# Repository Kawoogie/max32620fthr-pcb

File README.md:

# MAX32620FTHR PCB CAD Data

## Files
File Name | Description
--- | ---
max32620fthr.brd  | Cadsoft Eagle Board File (7.5.0)
max32620fthr.sch  | Cadsoft Eagle Schematic File (7.5.0)
output-gerb274x_4layer.cam  | Cadsoft Eagle CAM Job (7.5.0)
output/max32620fthr.gpi  | Photoplotter Info File
output/max32620fthr.GTL  | Top (1) copper
output/max32620fthr.GTS  | Top soldermask
output/max32620fthr.GTO  | Top silk screen
output/max32620fthr.GTP  | Top paste
output/max32620fthr.G2L  | Inner GND (2) copper
output/max32620fthr.G3L  | Inner PWR (15) copper
output/max32620fthr.GBL  | Bottom (16) copper
output/max32620fthr.GBS  | Bottom soldermask
output/max32620fthr.GBO  | Bottom silk screen
output/max32620fthr.GFD  | Fab drawing
output/max32620fthr.GML  | Mill Layer
output/max32620fthr.dri  | Drill Station Info File
output/max32620fthr.TXT  | Excellon Drill File
output/max32620fthr.mnt  | Component XY Data File
output/max32620fthr_sch.pdf  | PDF Schematic
output/max32620fthr_fab.PDF  | PDF Fab Drawing

## Bill Of Materials
[Octopart MAX32620FTHR BOM](https://octopart.com/bom-tool/neiQ2i4s)

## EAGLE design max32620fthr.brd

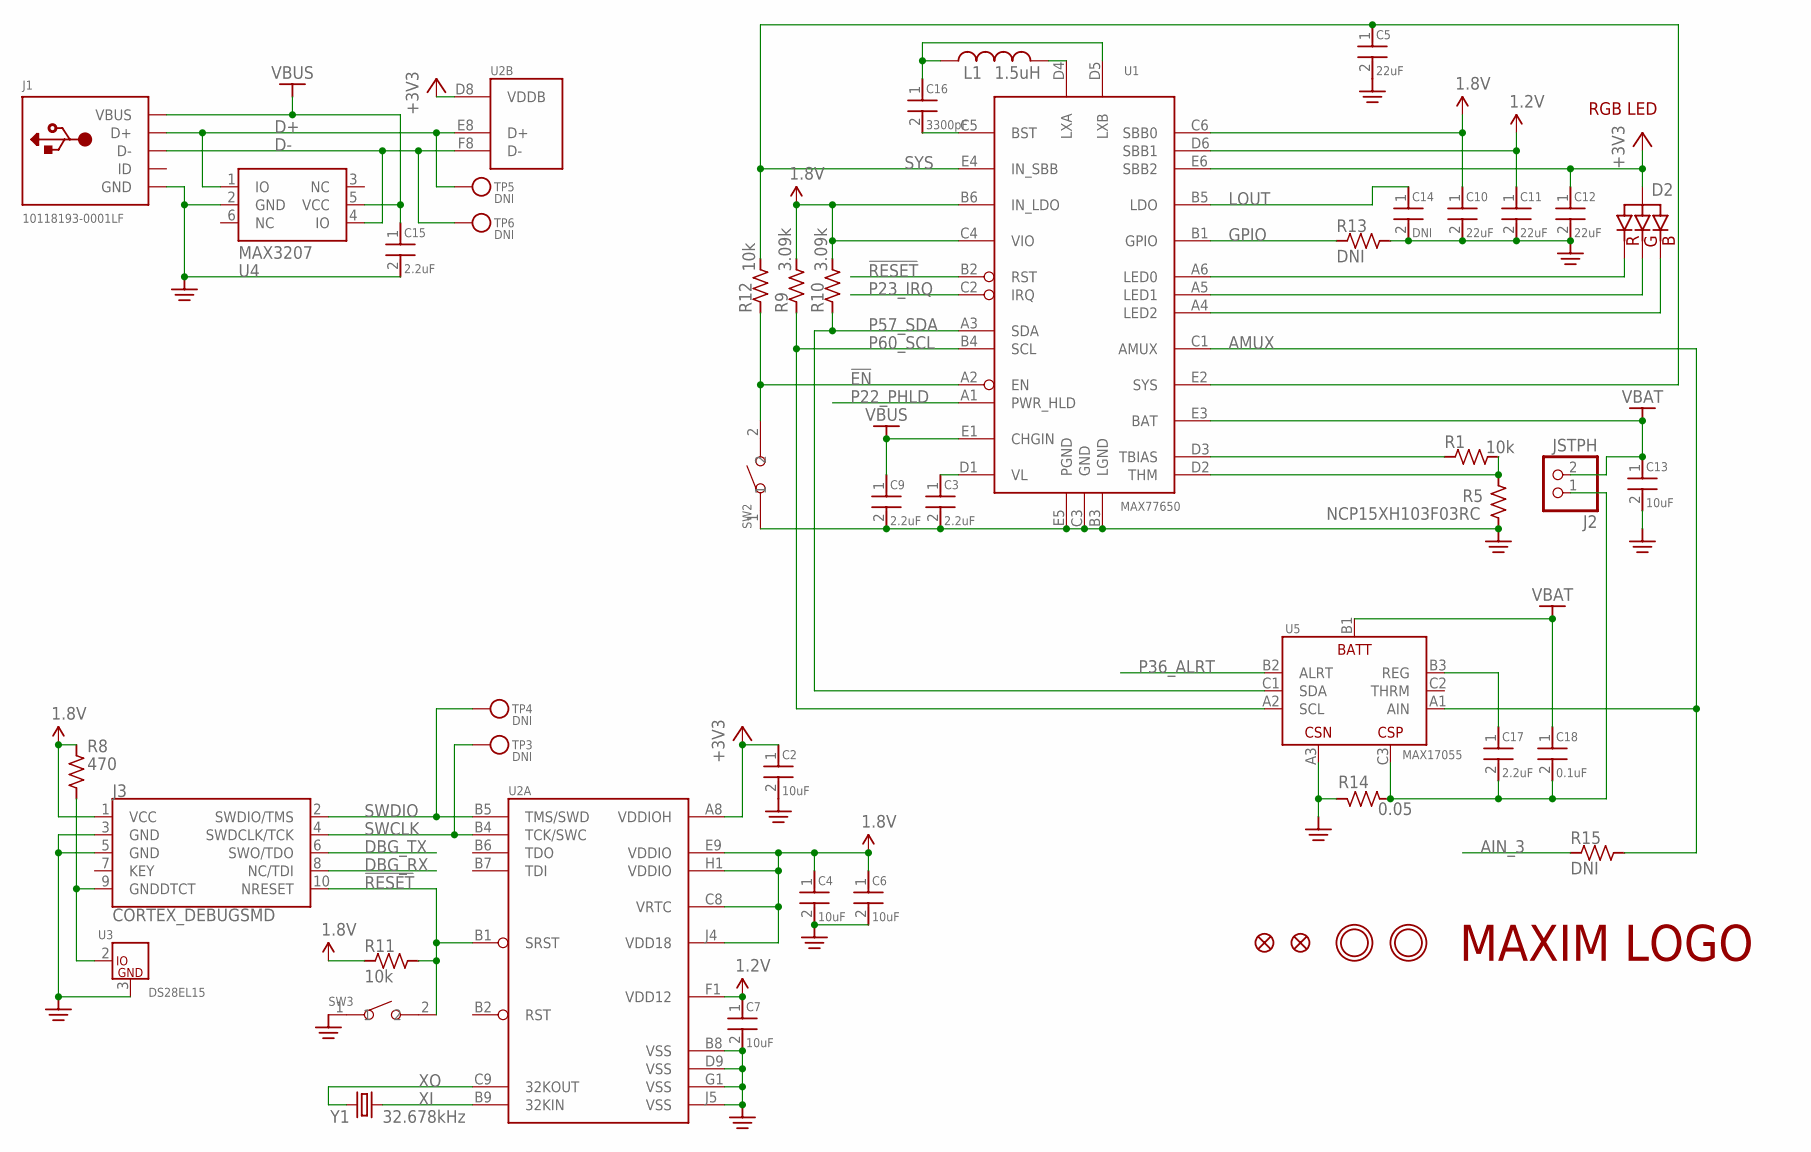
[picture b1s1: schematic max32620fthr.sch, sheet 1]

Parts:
C2, C4, C6, C7, C13: 10uF; 0402
C3, C9, C15, C17: 2.2uF; 0402
C5, C10, C11, C12: 22uF; 0402
C14: DNI; 0402
C16: 3300pF; 0402
C18: 0.1uF; 0402
D2: RGBLED_CALUMIX-SML-LX0404; LUMIX-SML-LX0404
J1: 10118193-0001LF; MICRO-USB5+6P-SMD-0.65-B
J2: JSTPH; JSTPH2
J3: CORTEX_DEBUGSMD; SAMTECH_FTSH-105-01
L1: 1.5uH; IND2016
R1, R11, R12: 10k; 0402
R5: NCP15XH103F03RC; 0402
R8: 470; 0402
R9, R10: 3.09k; 0402
R13, R15: DNI; 0402
R14: 0.05; 0402
SW2, SW3: SMD-BUTTON(2P-3.0X2.5X1.2+0.4MM)-B3U-1000P-2P-SMD; SW2-2.6-3.0X2.5X1.2+0.4MM
TP3, TP4, TP5, TP6: DNI; TESTPOINT_ROUND_1MM
U1: MAX77650; W302H2-1
U2: MAX32620; W813D3-1
U3: DS28EL15; T633-2
U4: MAX3207; SOT23-6
U5: MAX17055; W91N1-1
U$3: DNI; MXM_LOGO_6MM
U$31, U$32: DNI; MOUNTINGHOLE_2.5_PLATED
U$34, U$35: DNI; FIDUCIAL_1MM
Y1: 32.678kHz; FC-12M

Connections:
1.2V: C7.1, C11.1, U1.D6 (SBB1), U2.F1 (VDD12)
1.8V: C4.1, C6.1, C10.1, J3.1 (VCC), R8.2, R9.2, R10.2, R11.1, U1.B6 (IN_LDO), U1.C4 (VIO), U1.C6 (SBB0), U2.C8 (VRTC), U2.E9 (VDDIO), U2.H1 (VDDIO), U2.J4 (VDD18); also elsewhere on the board
!EN: R12.1, SW2.2, U1.A2 (EN); also elsewhere on the board
!RESET: J3.10 (NRESET), R11.2, SW3.2, U1.B2 (RST), U2.B1 (SRST); also elsewhere on the board
+3V3: C2.1, C12.1, D2.1 (VCC), U1.E6 (SBB2), U2.A8 (VDDIOH), U2.D8 (VDDB); also elsewhere on the board
AIN_3: R15.1; also elsewhere on the board
AMUX: R15.2, U1.C1 (AMUX), U5.A1 (AIN)
D+: J1.3 (D+), TP5.P$1, U2.E8 (D+), U4.1 (IO)
D-: J1.2 (D-), TP6.P$1, U2.F8 (D-), U4.4 (IO)
DBG_RX: J3.8 (NC/TDI); also elsewhere on the board
DBG_TX: J3.6 (SWO/TDO); also elsewhere on the board
GND: C2.2, C3.2, C4.2, C5.2, C6.2, C7.2, C9.2, C10.2, C11.2, C12.2, C13.2, C14.2, C15.2, J1.5 (GND), J1.S1 (GND), J1.S2 (GND), J1.S3 (GND), J1.S4 (GND), J1.S5 (GND), J1.S6 (GND), J3.3 (GND), J3.5 (GND), R5.2, R13.2, R14.2, SW2.1, SW3.1, U1.B3 (LGND), U1.C3 (GND), U1.E5 (PGND), U2.B8 (VSS), U2.D9 (VSS), U2.G1 (VSS), U2.J5 (VSS), U3.3 (GND), U4.2 (GND), U5.A3 (CSN); also elsewhere on the board
GPIO: R13.1, U1.B1 (GPIO)
LOUT: C14.1, U1.B5 (LDO)
unnamed: D2.2 (RED), U1.A6 (LED0)
unnamed: D2.4 (GREEN), U1.A5 (LED1)
unnamed: D2.3 (BLUE), U1.A4 (LED2)
unnamed: C3.1, U1.D1 (VL)
unnamed: R1.2, R5.1, U1.D2 (THM)
unnamed: R1.1, U1.D3 (TBIAS)
unnamed: J3.9 (GNDDTCT), R8.1, U3.2 (IO)
unnamed: C17.2, C18.2, J2.1, R14.1, U5.C3 (CSP)
unnamed: C17.1, U5.B3 (REG)
unnamed: C16.2, U1.C5 (BST)
unnamed: C16.1, L1.1, U1.D5 (LXB)
unnamed: L1.2, U1.D4 (LXA)
P22_PHLD: U1.A1 (PWR_HLD); also elsewhere on the board
P23_IRQ: U1.C2 (IRQ); also elsewhere on the board
P36_ALRT: U5.B2 (ALRT); also elsewhere on the board
P57_SDA: R10.1, U1.A3 (SDA), U5.C1 (SDA); also elsewhere on the board
P60_SCL: R9.1, U1.B4 (SCL), U5.A2 (SCL); also elsewhere on the board
SWCLK: J3.4 (SWDCLK/TCK), TP3.P$1, U2.B4 (TCK/SWC)
SWDIO: J3.2 (SWDIO/TMS), TP4.P$1, U2.B5 (TMS/SWD)
SYS: C5.1, R12.2, U1.E2 (SYS), U1.E4 (IN_SBB); also elsewhere on the board
VBAT: C13.1, C18.1, J2.2, U1.E3 (BAT), U5.B1 (BATT); also elsewhere on the board
VBUS: C9.1, C15.1, J1.1 (VBUS), U1.E1 (CHGIN), U4.5 (VCC); also elsewhere on the board
XI: U2.B9 (32KIN), Y1.2
XO: U2.C9 (32KOUT), Y1.1

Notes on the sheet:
RGB LED

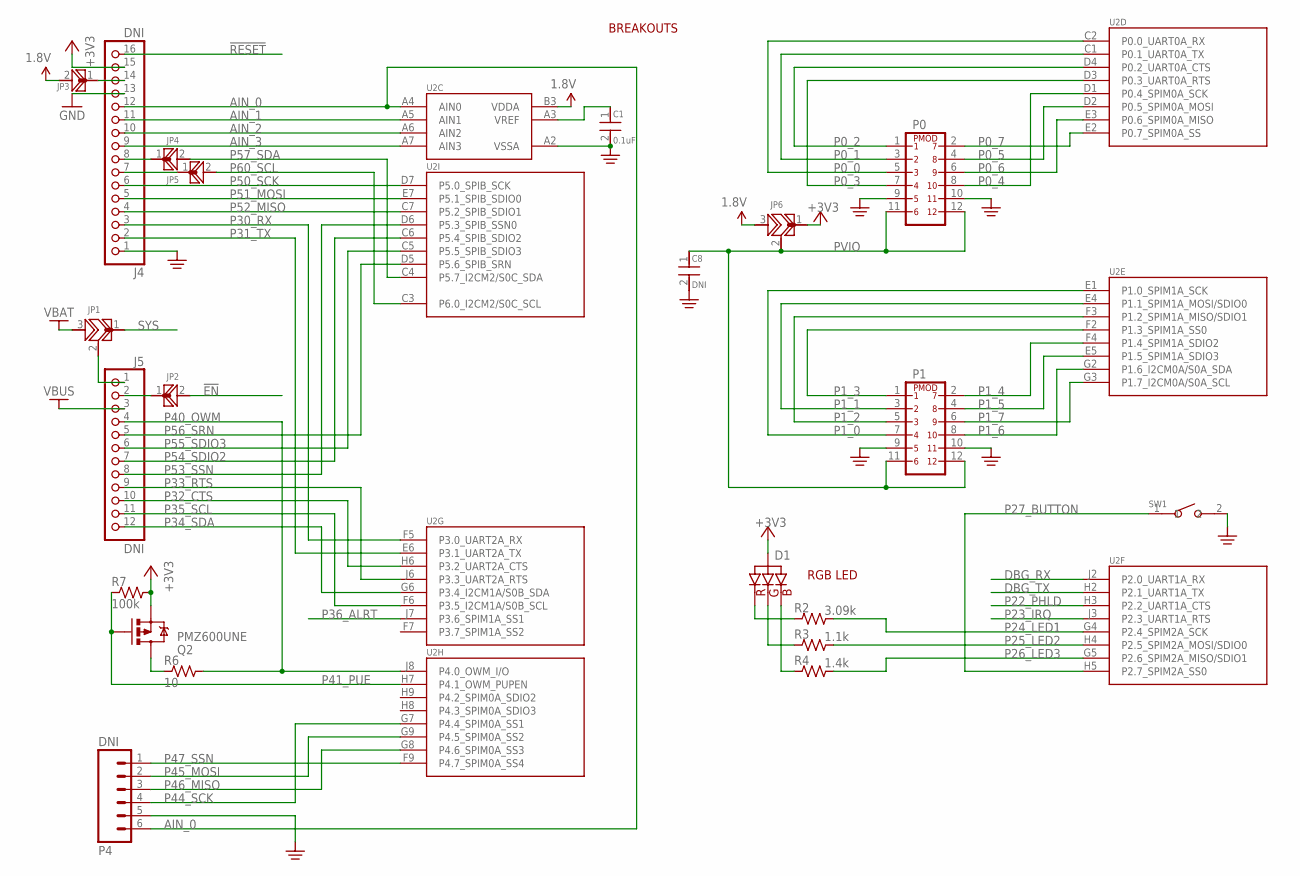
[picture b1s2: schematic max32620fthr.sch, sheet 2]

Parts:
C1: 0.1uF; 0402
C8: DNI; 0402
D1: RGBLED_CALUMIX-SML-LX0404; LUMIX-SML-LX0404
J4: DNI; 1X16_ROUND
J5: DNI; 1X12_ROUND
JP1, JP6: DNI; SS0402
JP2, JP3, JP4, JP5: DNI; SB0402
P0, P1: PMOD_DUALPASSTHROUGH; 2X6_HLE_BE
P4: DNI; 1X06-SMD_EDGE
Q2: PMZ600UNE; SOT-883
R2: 3.09k; 0402
R3: 1.1k; 0402
R4: 1.4k; 0402
R6: 10; 0402
R7: 100k; 0402
SW1: SMD-BUTTON(2P-3.0X2.5X1.2+0.4MM)-B3U-1000P-2P-SMD; SW2-2.6-3.0X2.5X1.2+0.4MM
U2: MAX32620; W813D3-1

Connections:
1.8V: JP3.2, JP6.3, U2.B3 (VDDA); also elsewhere on the board
!EN: JP2.2; also elsewhere on the board
!RESET: J4.16; also elsewhere on the board
+3V3: D1.1 (VCC), J4.15, JP6.1, Q2.2 (S), R7.2; also elsewhere on the board
AIN_0: J4.12, P4.6, U2.A4 (AIN0)
AIN_1: J4.11, U2.A5 (AIN1)
AIN_2: J4.10, U2.A6 (AIN2)
AIN_3: J4.9, U2.A7 (AIN3); also elsewhere on the board
DBG_RX: U2.J2 (P2.0_UART1A_RX); also elsewhere on the board
DBG_TX: U2.H2 (P2.1_UART1A_TX); also elsewhere on the board
GND: C1.2, C8.2, J4.1, J4.13, P0.9, P0.10, P1.9, P1.10, P4.5, SW1.2, U2.A2 (VSSA); also elsewhere on the board
unnamed: J4.8, JP4.1
unnamed: J4.7, JP5.1
unnamed: J4.14, JP3.1
unnamed: J5.2, JP2.1
unnamed: J5.1, JP1.2
unnamed: D1.2 (RED), R2.1
unnamed: D1.4 (GREEN), R3.1
unnamed: D1.3 (BLUE), R4.1
unnamed: Q2.3 (D), R6.1
unnamed: C1.1, U2.A3 (VREF)
P0_0: P0.5, U2.C2 (P0.0_UART0A_RX)
P0_1: P0.3, U2.C1 (P0.1_UART0A_TX)
P0_2: P0.1, U2.D4 (P0.2_UART0A_CTS)
P0_3: P0.7, U2.D3 (P0.3_UART0A_RTS)
P0_4: P0.8, U2.D1 (P0.4_SPIM0A_SCK)
P0_5: P0.4, U2.D2 (P0.5_SPIM0A_MOSI)
P0_6: P0.6, U2.E3 (P0.6_SPIM0A_MISO)
P0_7: P0.2, U2.E2 (P0.7_SPIM0A_SS)
P1_0: P1.7, U2.E1 (P1.0_SPIM1A_SCK)
P1_1: P1.3, U2.E4 (P1.1_SPIM1A_MOSI/SDIO0)
P1_2: P1.5, U2.F3 (P1.2_SPIM1A_MISO/SDIO1)
P1_3: P1.1, U2.F2 (P1.3_SPIM1A_SS0)
P1_4: P1.2, U2.F4 (P1.4_SPIM1A_SDIO2)
P1_5: P1.4, U2.E5 (P1.5_SPIM1A_SDIO3)
P1_6: P1.8, U2.G2 (P1.6_I2CM0A/S0A_SDA)
P1_7: P1.6, U2.G3 (P1.7_I2CM0A/S0A_SCL)
P22_PHLD: U2.H3 (P2.2_UART1A_CTS); also elsewhere on the board
P23_IRQ: U2.J3 (P2.3_UART1A_RTS); also elsewhere on the board
P24_LED1: R2.2, U2.G4 (P2.4_SPIM2A_SCK)
P25_LED2: R3.2, U2.H4 (P2.5_SPIM2A_MOSI/SDIO0)
P26_LED3: R4.2, U2.G5 (P2.6_SPIM2A_MISO/SDIO1)
P27_BUTTON: SW1.1, U2.H5 (P2.7_SPIM2A_SS0)
P30_RX: J4.3, U2.F5 (P3.0_UART2A_RX)
P31_TX: J4.2, U2.E6 (P3.1_UART2A_TX)
P32_CTS: J5.10, U2.H6 (P3.2_UART2A_CTS)
P33_RTS: J5.9, U2.J6 (P3.3_UART2A_RTS)
P34_SDA: J5.12, U2.G6 (P3.4_I2CM1A/S0B_SDA)
P35_SCL: J5.11, U2.F6 (P3.5_I2CM1A/S0B_SCL)
P36_ALRT: U2.J7 (P3.6_SPIM1A_SS1); also elsewhere on the board
P40_OWM: J5.4, R6.2, U2.J8 (P4.0_OWM_I/O)
P41_PUE: Q2.1 (G), R7.1, U2.H7 (P4.1_OWM_PUPEN)
P44_SCK: P4.4, U2.G7 (P4.4_SPIM0A_SS1)
P45_MOSI: P4.2, U2.G9 (P4.5_SPIM0A_SS2)
P46_MISO: P4.3, U2.G8 (P4.6_SPIM0A_SS3)
P47_SSN: P4.1, U2.F9 (P4.7_SPIM0A_SS4)
P50_SCK: J4.6, U2.D7 (P5.0_SPIB_SCK)
P51_MOSI: J4.5, U2.E7 (P5.1_SPIB_SDIO0)
P52_MISO: J4.4, U2.C7 (P5.2_SPIB_SDIO1)
P53_SSN: J5.8, U2.D6 (P5.3_SPIB_SSN0)
P54_SDIO2: J5.7, U2.C6 (P5.4_SPIB_SDIO2)
P55_SDIO3: J5.6, U2.C5 (P5.5_SPIB_SDIO3)
P56_SRN: J5.5, U2.D5 (P5.6_SPIB_SRN)
P57_SDA: JP4.2, U2.C4 (P5.7_I2CM2/S0C_SDA); also elsewhere on the board
P60_SCL: JP5.2, U2.C3 (P6.0_I2CM2/S0C_SCL); also elsewhere on the board
PVIO: C8.1, JP6.2, P0.11, P0.12, P1.11, P1.12
SYS: JP1.1; also elsewhere on the board
VBAT: JP1.3; also elsewhere on the board
VBUS: J5.3; also elsewhere on the board

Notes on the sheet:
BREAKOUTS
RGB LED

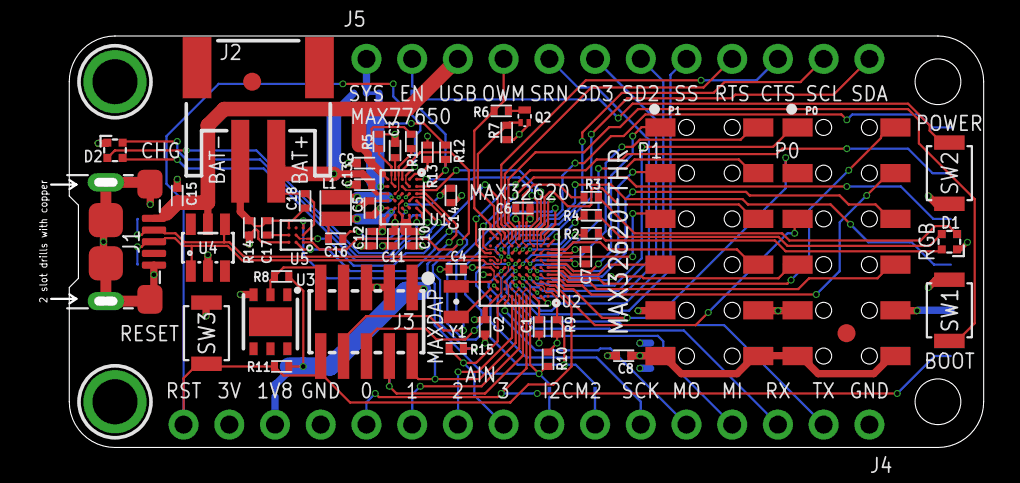
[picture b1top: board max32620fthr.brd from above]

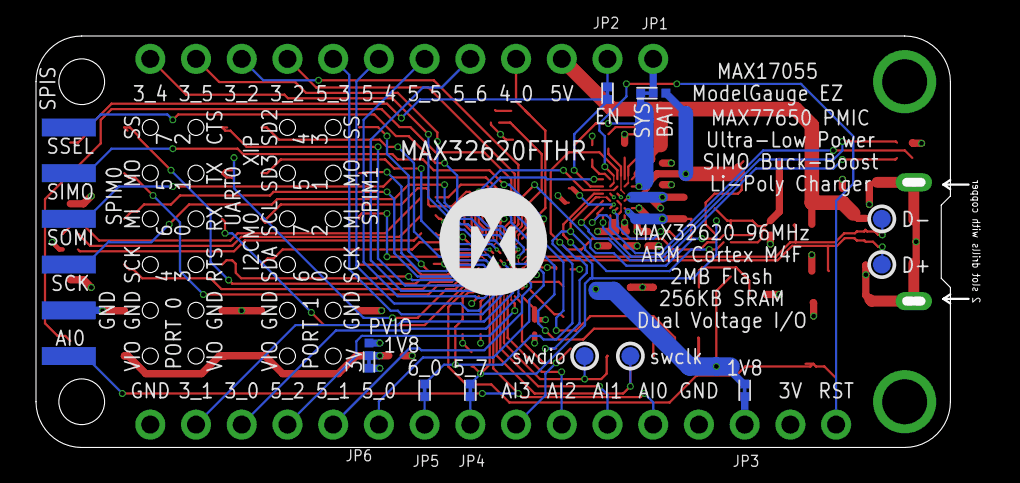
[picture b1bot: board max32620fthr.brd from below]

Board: 4 copper layers, 52.1 x 22.4 mm, 70 parts (12 on the bottom side), 91 nets.

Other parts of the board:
DRILEGEND: DRILEGEND

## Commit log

2018-01-21 addign cam job anand readme
2018-01-21 re-adding README.md for upload

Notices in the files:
parts and their libraries:
microbuilder: This work is placed in the public domain, and may be freely used for commercial and non-commercial work with the following conditions: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
SparkFun-Connectors: Licensing: Creative Commons ShareAlike 4.0 International - https://creativecommons.org/licenses/by-sa/4.0
